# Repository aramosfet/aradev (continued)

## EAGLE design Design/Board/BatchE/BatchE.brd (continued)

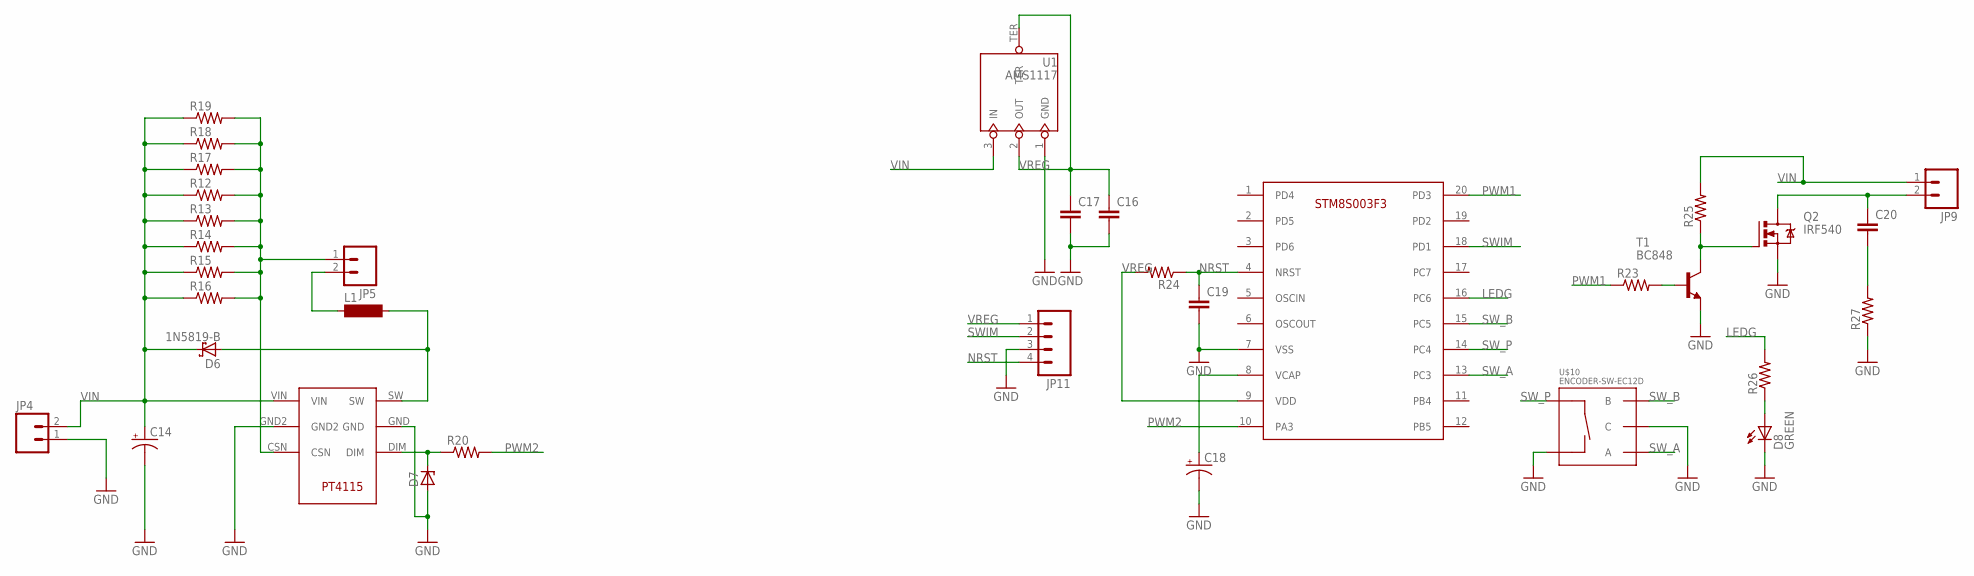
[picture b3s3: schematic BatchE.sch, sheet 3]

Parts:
C14: CAP_POLPTH4; CPOL-RADIAL-1000UF-25V
C16, C17, C19, C20: CAP1206; 1206
C18: CAP_POLPTH2; CPOL-RADIAL-10UF-25V
D6: 1N5819-B; DO41-7.6
D7: ZENER-DIODEZD-7.5; ZDIO-7.5
D8: GREEN; LED-1206
JP4, JP5, JP9: M02LOCK_LONGPADS; 1X02_LOCK_LONGPADS
JP11: M04PTH; 1X04
L1: BS11
Q2: IRF540; TO220BV
R12, R13, R14, R15, R16, R17, R18, R19, R20: RESISTOR1206; 1206
R23, R24, R25, R26, R27: RESISTOR0805-RES; 0805
T1: BC848; SOT23
U1: AMS1117; SOT-223
U$6: PT4115
U$9: STM8S003F3; SSOP20
U$10: ENCODER-SW-EC12D

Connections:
GND: C14.2 (-), C16.2, C17.2, C18.2 (-), C19.2, D7.A, D8.C, JP4.1, JP11.3, Q2.S, R27.1, T1.2 (E), U1.1 (GND), U$6.GND, U$6.GND2, U$9.7 (VSS), U$10.4 (C), U$10.5 (SW-); also elsewhere on the board
LEDG: R26.2, U$9.16 (PC6)
unnamed: JP5.1, R12.2, R13.2, R14.2, R15.2, R16.2, R17.2, R18.2, R19.2, U$6.CSN
unnamed: D8.A, R26.1
unnamed: Q2.G, R25.1, T1.3 (C)
unnamed: D7.C, R20.1, U$6.DIM
unnamed: C20.2, R27.2
unnamed: D6.A, L1.2, U$6.SW
unnamed: JP5.2, L1.1
unnamed: C20.1, JP9.2, Q2.D
unnamed: C18.1 (+), U$9.8 (VCAP)
unnamed: R23.2, T1.1 (B)
NRST: C19.1, JP11.4, R24.1, U$9.4 (NRST)
PWM1: R23.1, U$9.20 (PD3)
PWM2: R20.2, U$9.10 (PA3)
SWIM: JP11.2, U$9.18 (PD1)
SW_A: U$9.13 (PC3), U$10.1 (A)
SW_B: U$9.15 (PC5), U$10.3 (B)
SW_P: U$9.14 (PC4), U$10.2 (SW+)
VIN: C14.1 (+), D6.C, JP4.2, JP9.1, R12.1, R13.1, R14.1, R15.1, R16.1, R17.1, R18.1, R19.1, R25.2, U1.3 (IN), U$6.VIN
VREG: C16.1, C17.1, JP11.1, R24.2, U1.2 (OUT), U1.TER, U$9.9 (VDD)

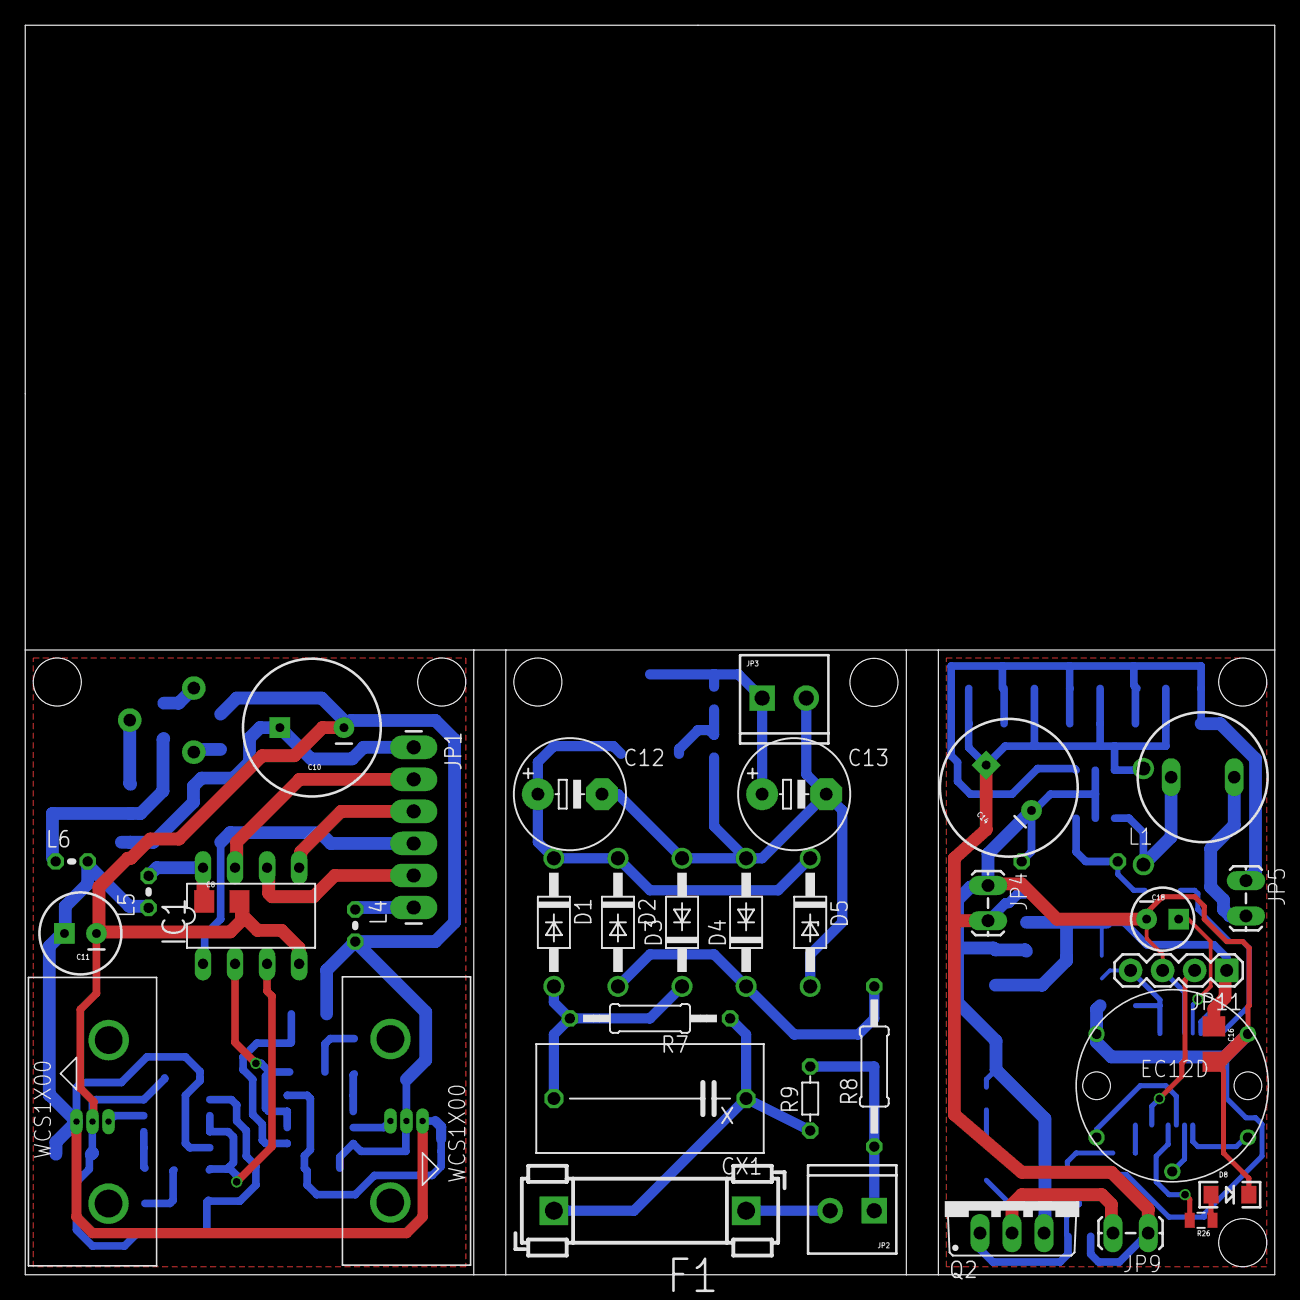
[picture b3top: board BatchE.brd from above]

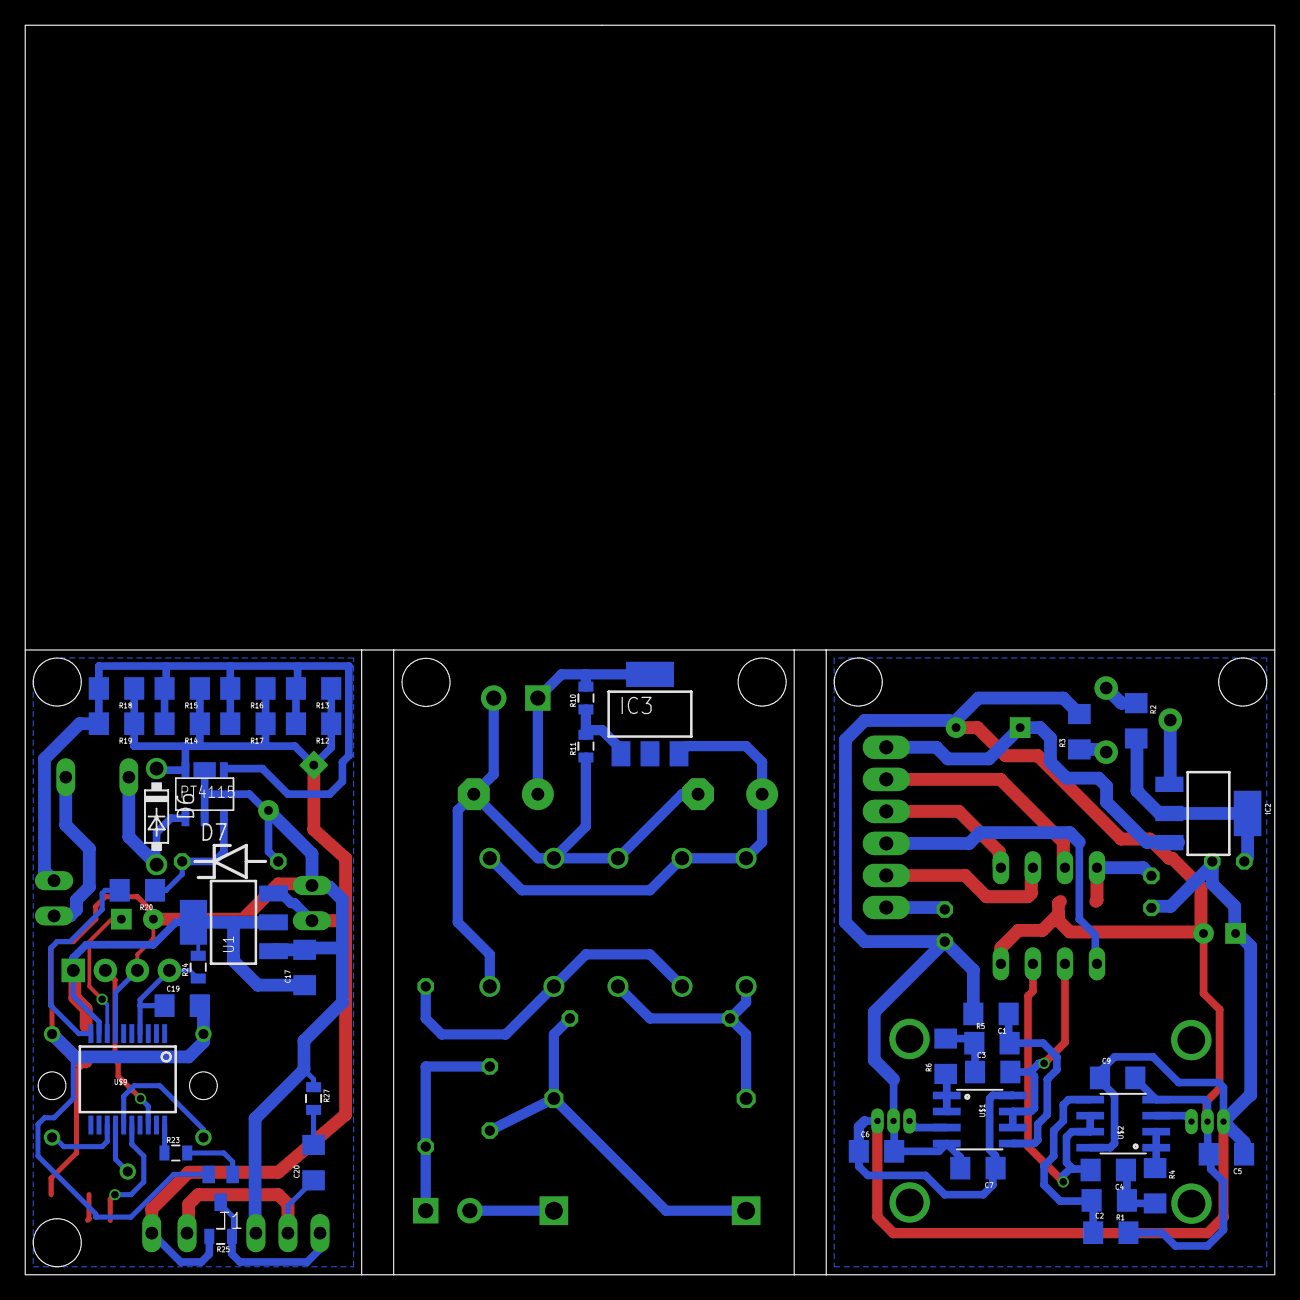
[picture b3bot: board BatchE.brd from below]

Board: 2 copper layers, 99.1 x 99.1 mm, 79 parts (42 on the bottom side), 52 nets.

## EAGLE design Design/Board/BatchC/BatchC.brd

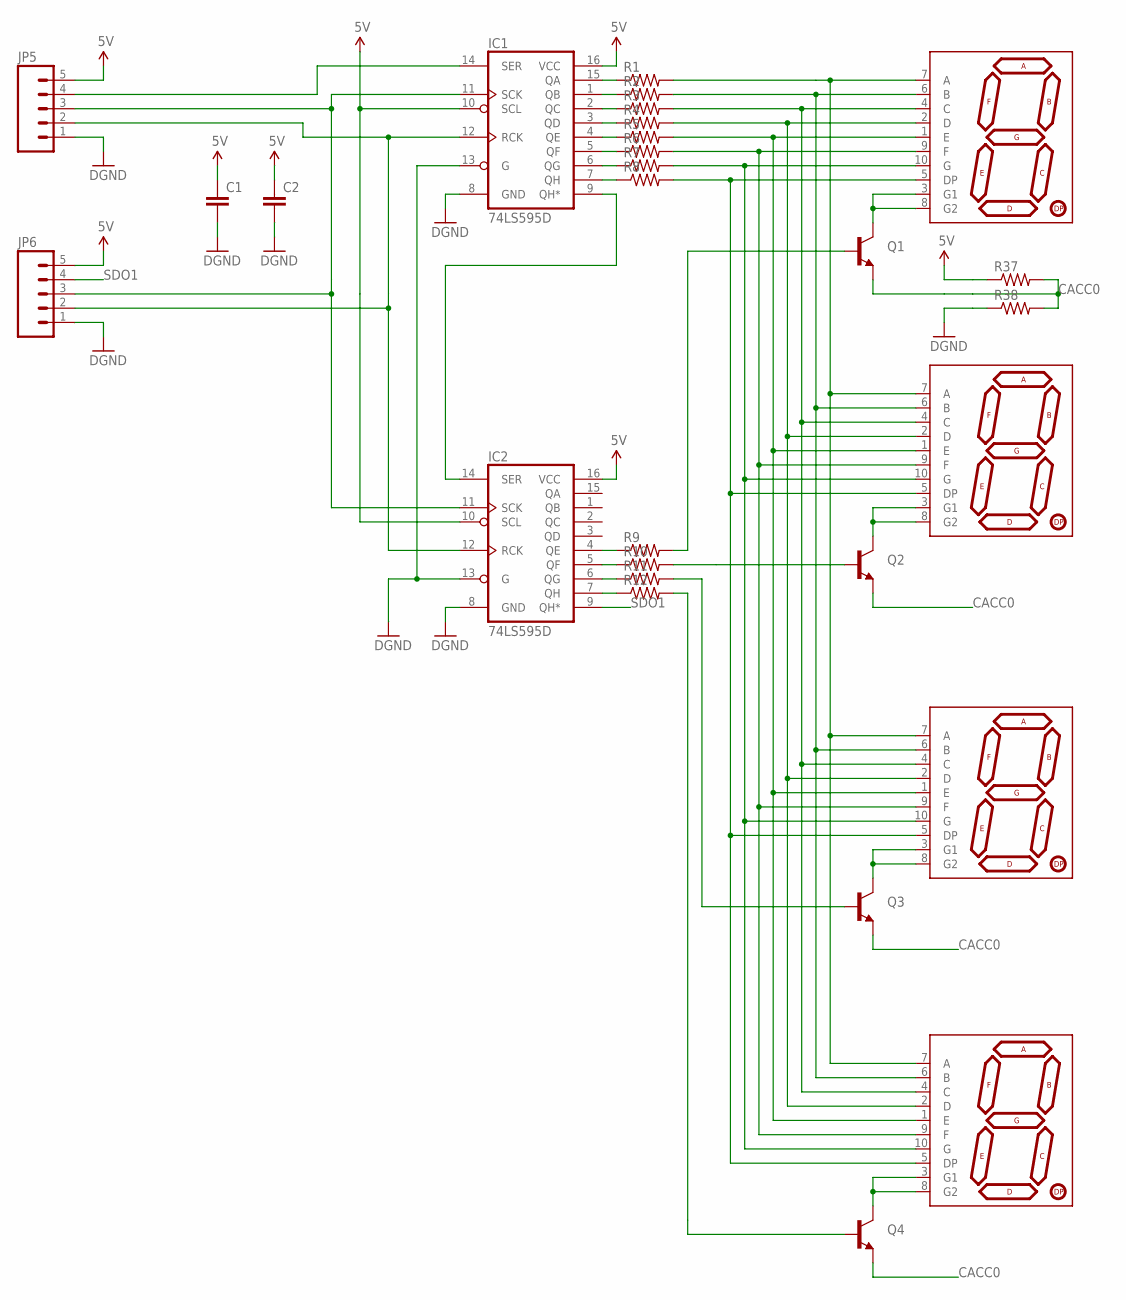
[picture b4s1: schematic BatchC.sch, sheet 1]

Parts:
C1, C2: CAP1206; 1206
IC1, IC2: 74LS595D; SO16
JP5, JP6: M05PTH; 1X05
Q1, Q2, Q3, Q4: TRANSISTOR_NPNSOT23; SOT23
R1, R2, R3, R4, R5, R6, R7, R8, R9, R10, R11, R12, R37, R38: RESISTOR0805-RES; 0805
U$1, U$2, U$3, U$4: 7-SEGMENT-DISPLAYPTH; 7-SEGMENT-DISPLAY

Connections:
5V: C1.1, C2.1, IC1.10 (SCL), IC1.16 (VCC), IC2.10 (SCL), IC2.16 (VCC), JP5.5, JP6.5, R37.1; also elsewhere on the board
CACC0: Q1.2 (E), Q2.2 (E), Q3.2 (E), Q4.2 (E), R37.2, R38.2
GND: C1.2, C2.2, IC1.8 (GND), IC1.13 (G), IC2.8 (GND), IC2.13 (G), JP5.1, JP6.1, R38.1; also elsewhere on the board
unnamed: Q2.3 (C), U$1.3 (G1), U$1.8 (G2)
unnamed: Q3.3 (C), U$2.3 (G1), U$2.8 (G2)
unnamed: Q4.3 (C), U$4.3 (G1), U$4.8 (G2)
unnamed: R4.2, U$1.2 (D), U$2.2 (D), U$3.2 (D), U$4.2 (D)
unnamed: R5.2, U$1.1 (E), U$2.1 (E), U$3.1 (E), U$4.1 (E)
unnamed: R6.2, U$1.9 (F), U$2.9 (F), U$3.9 (F), U$4.9 (F)
unnamed: R7.2, U$1.10 (G), U$2.10 (G), U$3.10 (G), U$4.10 (G)
unnamed: R8.2, U$1.5 (DP), U$2.5 (DP), U$3.5 (DP), U$4.5 (DP)
unnamed: IC1.15 (QA), R1.1
unnamed: IC1.1 (QB), R2.1
unnamed: IC1.2 (QC), R3.1
unnamed: IC1.3 (QD), R4.1
unnamed: IC1.4 (QE), R5.1
unnamed: IC1.5 (QF), R6.1
unnamed: IC1.6 (QG), R7.1
unnamed: IC1.7 (QH), R8.1
unnamed: Q1.3 (C), U$3.3 (G1), U$3.8 (G2)
unnamed: R3.2, U$1.4 (C), U$2.4 (C), U$3.4 (C), U$4.4 (C)
unnamed: R2.2, U$1.6 (B), U$2.6 (B), U$3.6 (B), U$4.6 (B)
unnamed: R1.2, U$1.7 (A), U$2.7 (A), U$3.7 (A), U$4.7 (A)
unnamed: IC2.7 (QH), R12.1
unnamed: IC2.6 (QG), R11.1
unnamed: IC2.5 (QF), R10.1
unnamed: IC2.4 (QE), R9.1
unnamed: Q3.1 (B), R11.2
unnamed: Q2.1 (B), R10.2
unnamed: Q4.1 (B), R12.2
unnamed: Q1.1 (B), R9.2
unnamed: IC1.12 (RCK), IC2.12 (RCK), JP5.2, JP6.2
unnamed: IC1.14 (SER), JP5.4
unnamed: IC1.11 (SCK), IC2.11 (SCK), JP5.3, JP6.3
unnamed: IC1.9 (QH*), IC2.14 (SER)
SDO1: IC2.9 (QH*), JP6.4

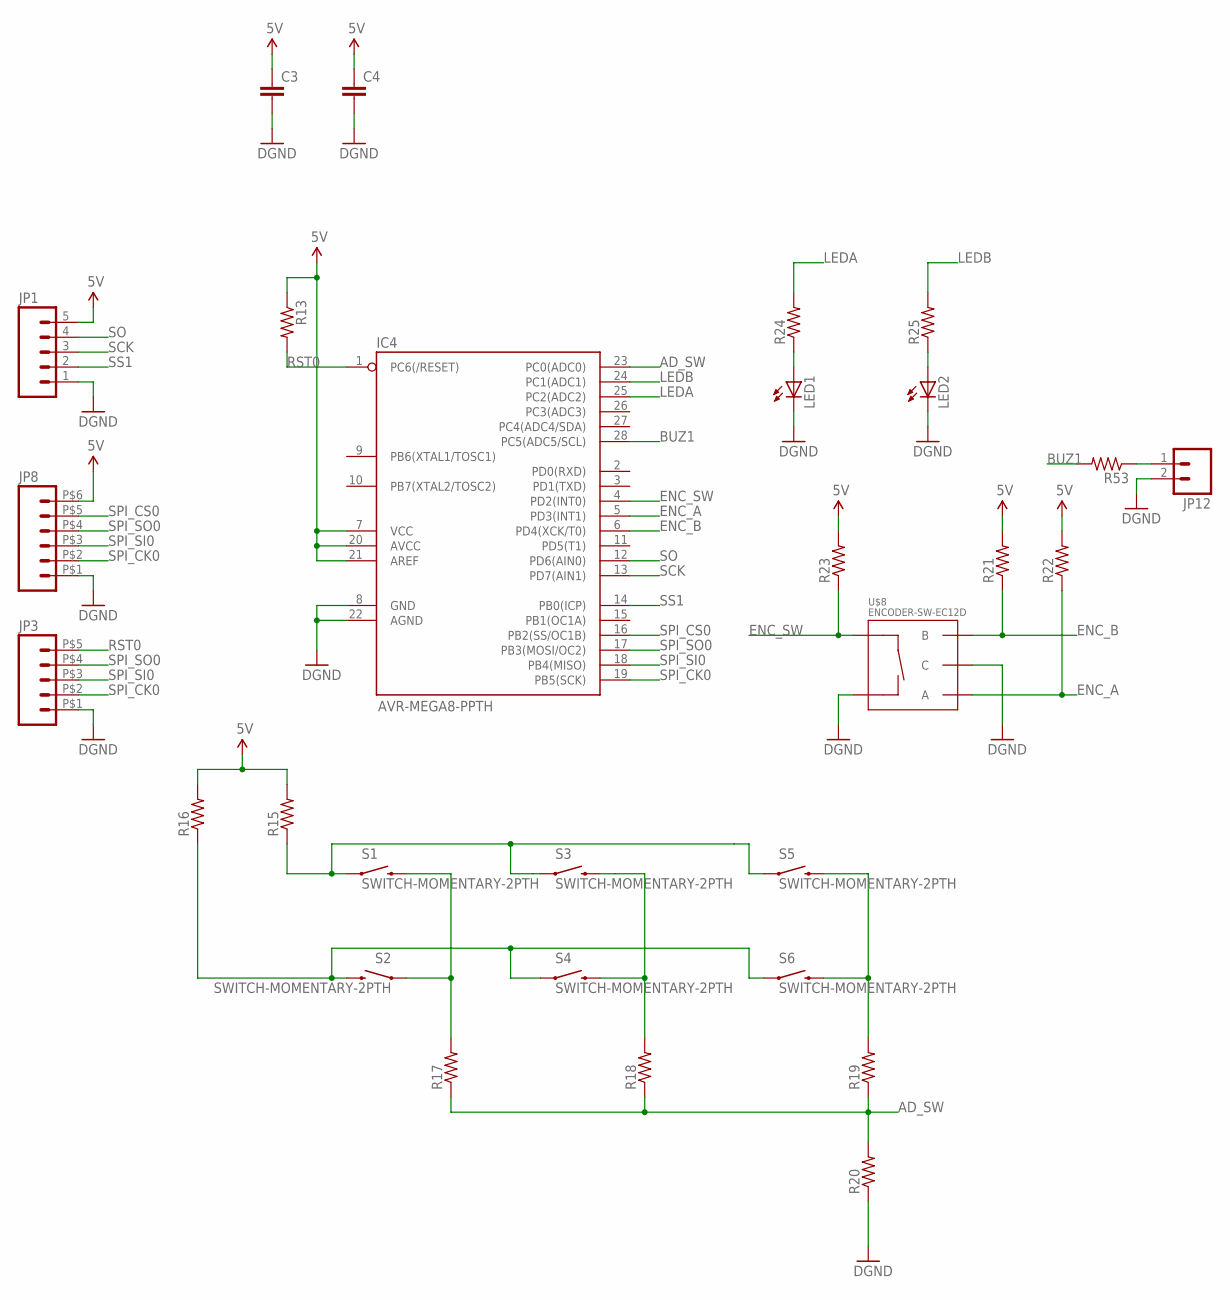
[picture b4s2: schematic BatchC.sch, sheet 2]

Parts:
C3, C4: CAP1206; 1206
IC4: AVR-MEGA8-PPTH; DIL28-3
JP1: M05PTH; 1X05
JP3: M05; 1X05_SMALLPADS
JP8: M06; 1X06_SMALLPADS
JP12: M02PTH; 1X02
LED1, LED2: LED3MM
R13, R15, R16, R17, R18, R19, R20, R21, R22, R23, R24, R25, R53: RESISTOR0805-RES; 0805
S1, S2, S3, S4, S5, S6: SWITCH-MOMENTARY-2PTH; TACTILE-PTH
U$8: ENCODER-SW-EC12D

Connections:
5V: C3.1, C4.1, IC4.7 (VCC), IC4.20 (AVCC), IC4.21 (AREF), JP1.5, JP8.P$6 (6), R13.1, R15.2, R16.2, R21.2, R22.2, R23.2; also elsewhere on the board
AD_SW: IC4.23 (PC0(ADC0)), R17.1, R18.1, R19.1, R20.2
BUZ1: IC4.28 (PC5(ADC5/SCL)), R53.2
ENC_A: IC4.5 (PD3(INT1)), R22.1, U$8.1 (A)
ENC_B: IC4.6 (PD4(XCK/T0)), R21.1, U$8.3 (B)
ENC_SW: IC4.4 (PD2(INT0)), R23.1, U$8.2 (SW+)
GND: C3.2, C4.2, IC4.8 (GND), IC4.22 (AGND), JP1.1, JP3.P$1 (1), JP8.P$1 (1), JP12.2, LED1.K (C), LED2.K (C), R20.1, U$8.4 (C), U$8.5 (SW-); also elsewhere on the board
LEDA: IC4.25 (PC2(ADC2)), R24.2
LEDB: IC4.24 (PC1(ADC1)), R25.2
unnamed: R17.2, S1.3 (2), S2.1
unnamed: R16.1, S2.3 (2), S4.1, S6.1
unnamed: R15.1, S1.1, S3.1, S5.1
unnamed: R18.2, S3.3 (2), S4.3 (2)
unnamed: R19.2, S5.3 (2), S6.3 (2)
unnamed: LED1.A, R24.1
unnamed: LED2.A, R25.1
unnamed: JP12.1, R53.1
RST0: IC4.1 (PC6(/RESET)), JP3.P$5 (5), R13.2
SCK: IC4.13 (PD7(AIN1)), JP1.3
SO: IC4.12 (PD6(AIN0)), JP1.4
SPI_CK0: IC4.19 (PB5(SCK)), JP3.P$2 (2), JP8.P$2 (2)
SPI_CS0: IC4.16 (PB2(SS/OC1B)), JP8.P$5 (5)
SPI_SI0: IC4.18 (PB4(MISO)), JP3.P$3 (3), JP8.P$3 (3)
SPI_SO0: IC4.17 (PB3(MOSI/OC2)), JP3.P$4 (4), JP8.P$4 (4)
SS1: IC4.14 (PB0(ICP)), JP1.2

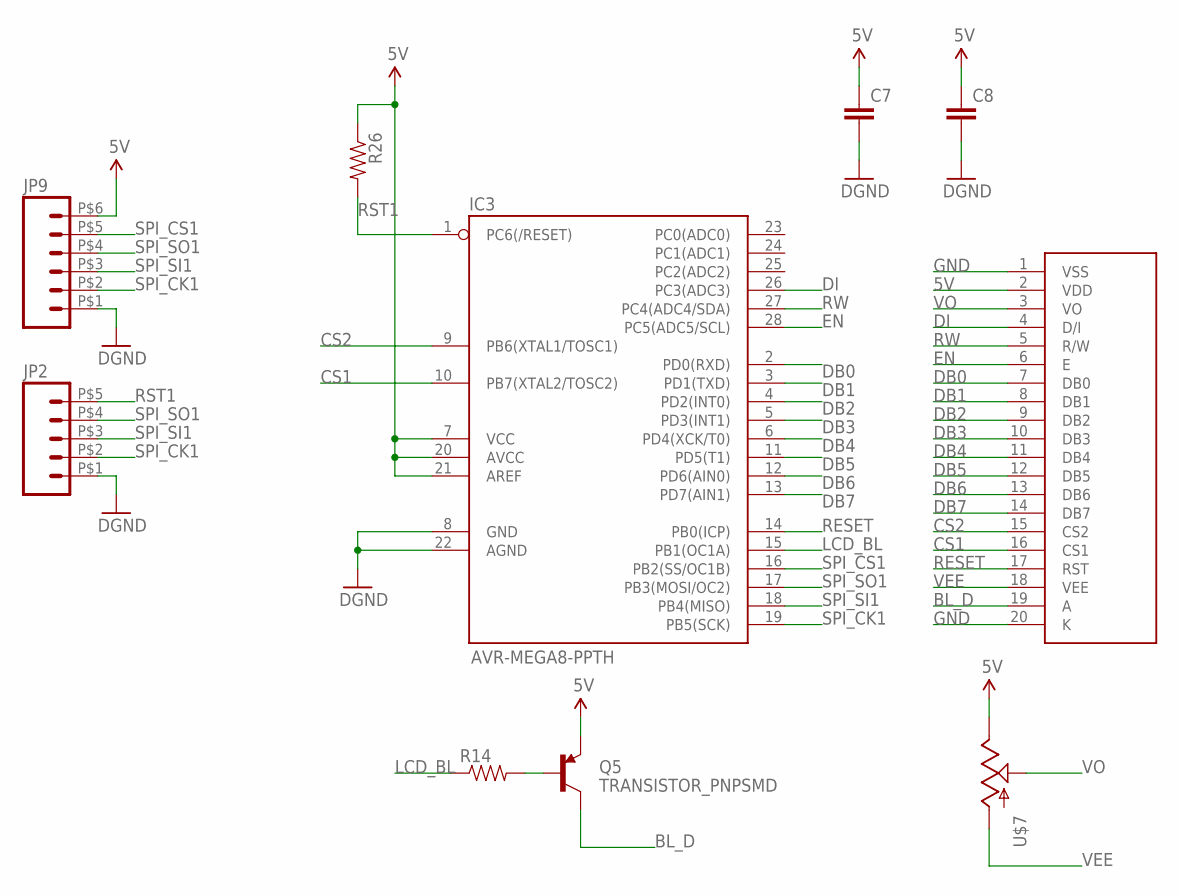
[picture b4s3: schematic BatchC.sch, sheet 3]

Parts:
C7, C8: CAP1206; 1206
IC3: AVR-MEGA8-PPTH; DIL28-3
JP2: M05; 1X05_SMALLPADS
JP9: M06; 1X06_SMALLPADS
Q5: TRANSISTOR_PNPSMD; SOT23-3
R14, R26: RESISTOR0805-RES; 0805
U$7: POTTRIM; TRIM_POT
U$9: LCD-G12864BARE; 1X20

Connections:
5V: C7.1, C8.1, IC3.7 (VCC), IC3.20 (AVCC), IC3.21 (AREF), JP9.P$6 (6), Q5.2 (E), R26.1, U$7.2 (E), U$9.2 (VDD); also elsewhere on the board
BL_D: Q5.3 (C), U$9.19 (A)
CS1: IC3.10 (PB7(XTAL2/TOSC2)), U$9.16 (CS1)
CS2: IC3.9 (PB6(XTAL1/TOSC1)), U$9.15 (CS2)
DB0: IC3.2 (PD0(RXD)), U$9.7 (DB0)
DB1: IC3.3 (PD1(TXD)), U$9.8 (DB1)
DB2: IC3.4 (PD2(INT0)), U$9.9 (DB2)
DB3: IC3.5 (PD3(INT1)), U$9.10 (DB3)
DB4: IC3.6 (PD4(XCK/T0)), U$9.11 (DB4)
DB5: IC3.11 (PD5(T1)), U$9.12 (DB5)
DB6: IC3.12 (PD6(AIN0)), U$9.13 (DB6)
DB7: IC3.13 (PD7(AIN1)), U$9.14 (DB7)
DI: IC3.26 (PC3(ADC3)), U$9.4 (D/I)
EN: IC3.28 (PC5(ADC5/SCL)), U$9.6 (E)
GND: C7.2, C8.2, IC3.8 (GND), IC3.22 (AGND), JP2.P$1 (1), JP9.P$1 (1), U$9.1 (VSS), U$9.20 (K); also elsewhere on the board
LCD_BL: IC3.15 (PB1(OC1A)), R14.1
unnamed: Q5.1 (B), R14.2
RESET: IC3.14 (PB0(ICP)), U$9.17 (RST)
RST1: IC3.1 (PC6(/RESET)), JP2.P$5 (5), R26.2
RW: IC3.27 (PC4(ADC4/SDA)), U$9.5 (R/W)
SPI_CK1: IC3.19 (PB5(SCK)), JP2.P$2 (2), JP9.P$2 (2)
SPI_CS1: IC3.16 (PB2(SS/OC1B)), JP9.P$5 (5)
SPI_SI1: IC3.18 (PB4(MISO)), JP2.P$3 (3), JP9.P$3 (3)
SPI_SO1: IC3.17 (PB3(MOSI/OC2)), JP2.P$4 (4), JP9.P$4 (4)
VEE: U$7.3 (A), U$9.18 (VEE)
VO: U$7.1 (S), U$9.3 (VO)

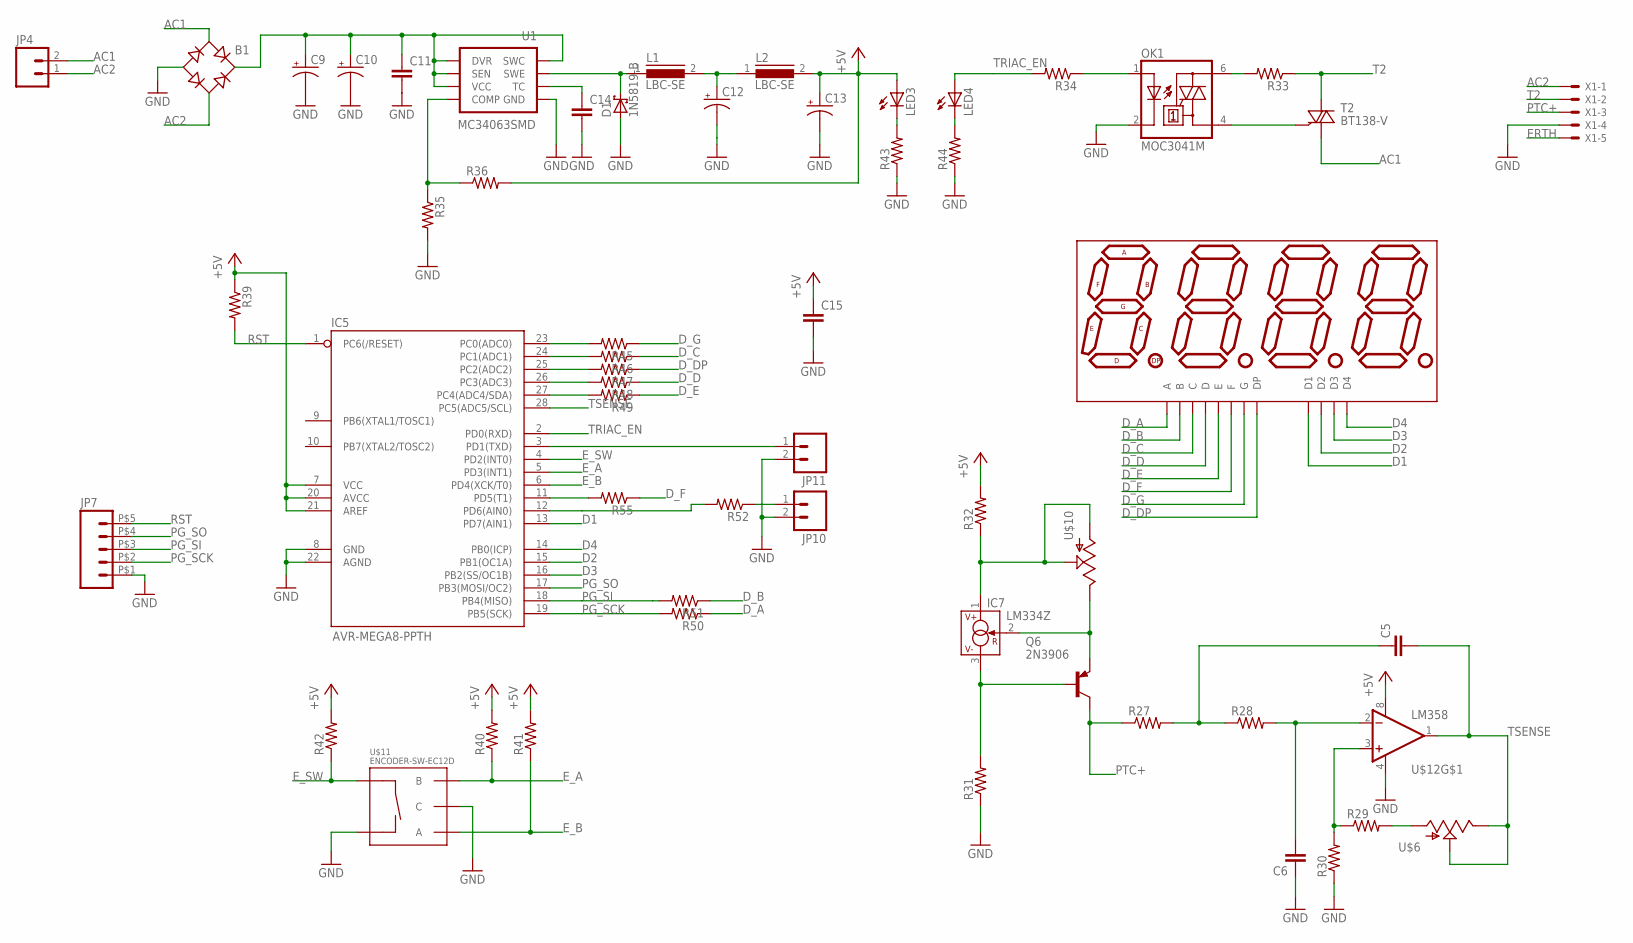
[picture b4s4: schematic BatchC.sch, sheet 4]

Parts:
B1: RB1A
C5, C6: CAPPTH; CAP-PTH-SMALL
C9, C10, C12, C13: CAP_POLPTH1; CPOL-RADIAL-100UF-25V
C11, C14, C15: CAP1206; 1206
D1: 1N5819-B; DO41-7.6
IC5: AVR-MEGA8-PPTH; DIL28-3
IC7: LM334Z; TO92
JP4: M023.5MM; SCREWTERMINAL-3.5MM-2
JP7: M05; 1X05_SMALLPADS
JP10, JP11: M02PTH; 1X02
L1, L2: LBC-SE
LED3, LED4: LED3MM
OK1: MOC3041M; DIL06
Q6: 2N3906; TO92
R27, R28, R29, R30, R31, R32, R33, R34, R35, R36, R39, R40, R41, R42, R43, R44, R45, R46, R47, R48, R49, R50, R51, R52, R55: RESISTOR0603-RES; 0603-RES
T2: BT138-V; TO220BV
U1: MC34063SMD; SO08
U$5: 7-SEGMENT-4DIGIT-COUNTER; 7-SEGMENT-4DIGIT-TPS
U$6, U$10: POTTRIM; TRIM_POT
U$11: ENCODER-SW-EC12D
U$12: LM358; DIP08
X1: KK-156-5

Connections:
+5V: C13.1 (+), C15.1, IC5.7 (VCC), IC5.20 (AVCC), IC5.21 (AREF), L2.2, LED3.A, R32.2, R36.2, R39.1, R40.2, R41.2, R42.2, U$12.8 (V+)
AC1: B1.AC1, JP4.2, T2.T1 (A1)
AC2: B1.AC2, JP4.1, X1.1
D1: IC5.13 (PD7(AIN1)), U$5.P$12 (D1)
D2: IC5.15 (PB1(OC1A)), U$5.P$9 (D2)
D3: IC5.16 (PB2(SS/OC1B)), U$5.P$8 (D3)
D4: IC5.14 (PB0(ICP)), U$5.P$6 (D4)
D_A: R50.1, U$5.P$11 (A)
D_B: R51.1, U$5.P$7 (B)
D_C: R46.1, U$5.P$4 (C)
D_D: R48.1, U$5.P$2 (D)
D_DP: R47.1, U$5.P$3 (DP)
D_E: R49.1, U$5.P$1 (E)
D_F: R55.1, U$5.P$10 (F)
D_G: R45.1, U$5.P$5 (G)
ERTH: X1.5
E_A: IC5.5 (PD3(INT1)), R40.1, U$11.3 (B)
E_B: IC5.6 (PD4(XCK/T0)), R41.1, U$11.1 (A)
E_SW: IC5.4 (PD2(INT0)), R42.1, U$11.2 (SW+)
GND: B1.-, C6.1, C9.2 (-), C10.2 (-), C11.2, C12.2 (-), C13.2 (-), C14.2, C15.2, D1.A, IC5.8 (GND), IC5.22 (AGND), JP7.P$1 (1), JP10.2, JP11.2, OK1.2 (C), R30.1, R31.1, R35.2, R43.1, R44.1, U1.4 (GND), U$11.4 (C), U$11.5 (SW-), U$12.4 (V-), X1.4; also elsewhere on the board
unnamed: IC7.3 (V-), Q6.2 (B), R31.2
unnamed: IC7.1 (V+), R32.1, U$10.1 (S), U$10.3 (A)
unnamed: IC5.24 (PC1(ADC1)), R46.2
unnamed: IC7.2 (R), Q6.3 (E), U$10.2 (E)
unnamed: OK1.1 (A), R34.1
unnamed: OK1.6 (A2), R33.2
unnamed: C5.1, R27.2, R28.1
unnamed: C6.2, R28.2, U$12.2 (-IN)
unnamed: IC5.25 (PC2(ADC2)), R47.2
unnamed: R29.2, U$6.3 (A)
unnamed: LED3.K (C), R43.2
unnamed: R29.1, R30.2, U$12.3 (+IN)
unnamed: OK1.4 (A1), T2.G
unnamed: LED4.K (C), R44.2
unnamed: B1.+, C9.1 (+), C10.1 (+), C11.1, U1.1 (SWC), U1.6 (VCC), U1.7 (SEN), U1.8 (DVR)
unnamed: C14.1, U1.3 (TC)
unnamed: D1.C, L1.1, U1.2 (SWE)
unnamed: C12.1 (+), L1.2, L2.1
unnamed: R35.1, R36.1, U1.5 (COMP)
unnamed: IC5.26 (PC3(ADC3)), R48.2
unnamed: IC5.27 (PC4(ADC4/SDA)), R49.2
unnamed: IC5.23 (PC0(ADC0)), R45.2
unnamed: IC5.11 (PD5(T1)), R55.2
unnamed: IC5.12 (PD6(AIN0)), R52.2
unnamed: JP10.1, R52.1
unnamed: IC5.3 (PD1(TXD)), JP11.1
PG_SCK: IC5.19 (PB5(SCK)), JP7.P$2 (2), R50.2
PG_SI: IC5.18 (PB4(MISO)), JP7.P$3 (3), R51.2
PG_SO: IC5.17 (PB3(MOSI/OC2)), JP7.P$4 (4)
PTC+: Q6.1 (C), R27.1, X1.3
RST: IC5.1 (PC6(/RESET)), JP7.P$5 (5), R39.2
T2: R33.1, T2.T2 (A2), X1.2
TRIAC_EN: IC5.2 (PD0(RXD)), LED4.A, R34.2
TSENSE: C5.2, IC5.28 (PC5(ADC5/SCL)), U$6.1 (S), U$6.2 (E), U$12.1 (OUT)

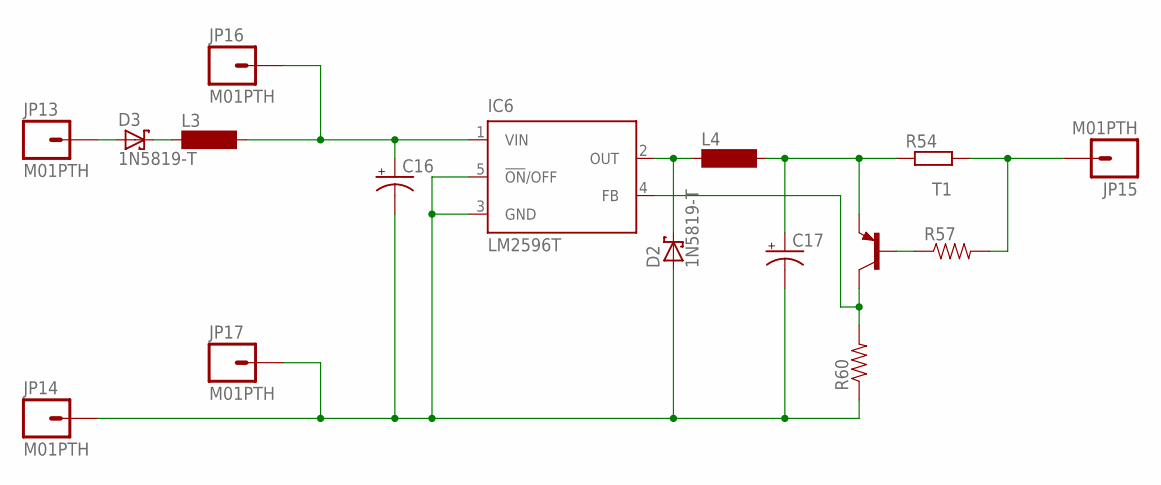
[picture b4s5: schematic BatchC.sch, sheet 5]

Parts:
C16, C17: CAP_POLPTH1; CPOL-RADIAL-100UF-25V
D2, D3: 1N5819-T; DO41-7.6
IC6: LM2596T; T05D
JP13, JP14, JP15, JP16, JP17: M01PTH; 1X01
L3, L4: BS11
R54: R-EU_0204/2V; 0204V
R57, R60: RESISTOR1206; 1206
T1: BC857C-PNP-SOT23-BEC; SOT23-BEC

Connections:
unnamed: D3.A, JP13.1
unnamed: D3.C, L3.1
unnamed: C16.1 (+), IC6.1 (VIN), JP16.1, L3.2
unnamed: C16.2 (-), C17.2 (-), D2.A, IC6.3 (GND), IC6.5 (!ON!/OFF), JP14.1, JP17.1, R60.1
unnamed: D2.C, IC6.2 (OUT), L4.1
unnamed: C17.1 (+), L4.2, R54.1, T1.E
unnamed: IC6.4 (FB), R60.2, T1.C
unnamed: R57.1, T1.B
unnamed: JP15.1, R54.2, R57.2

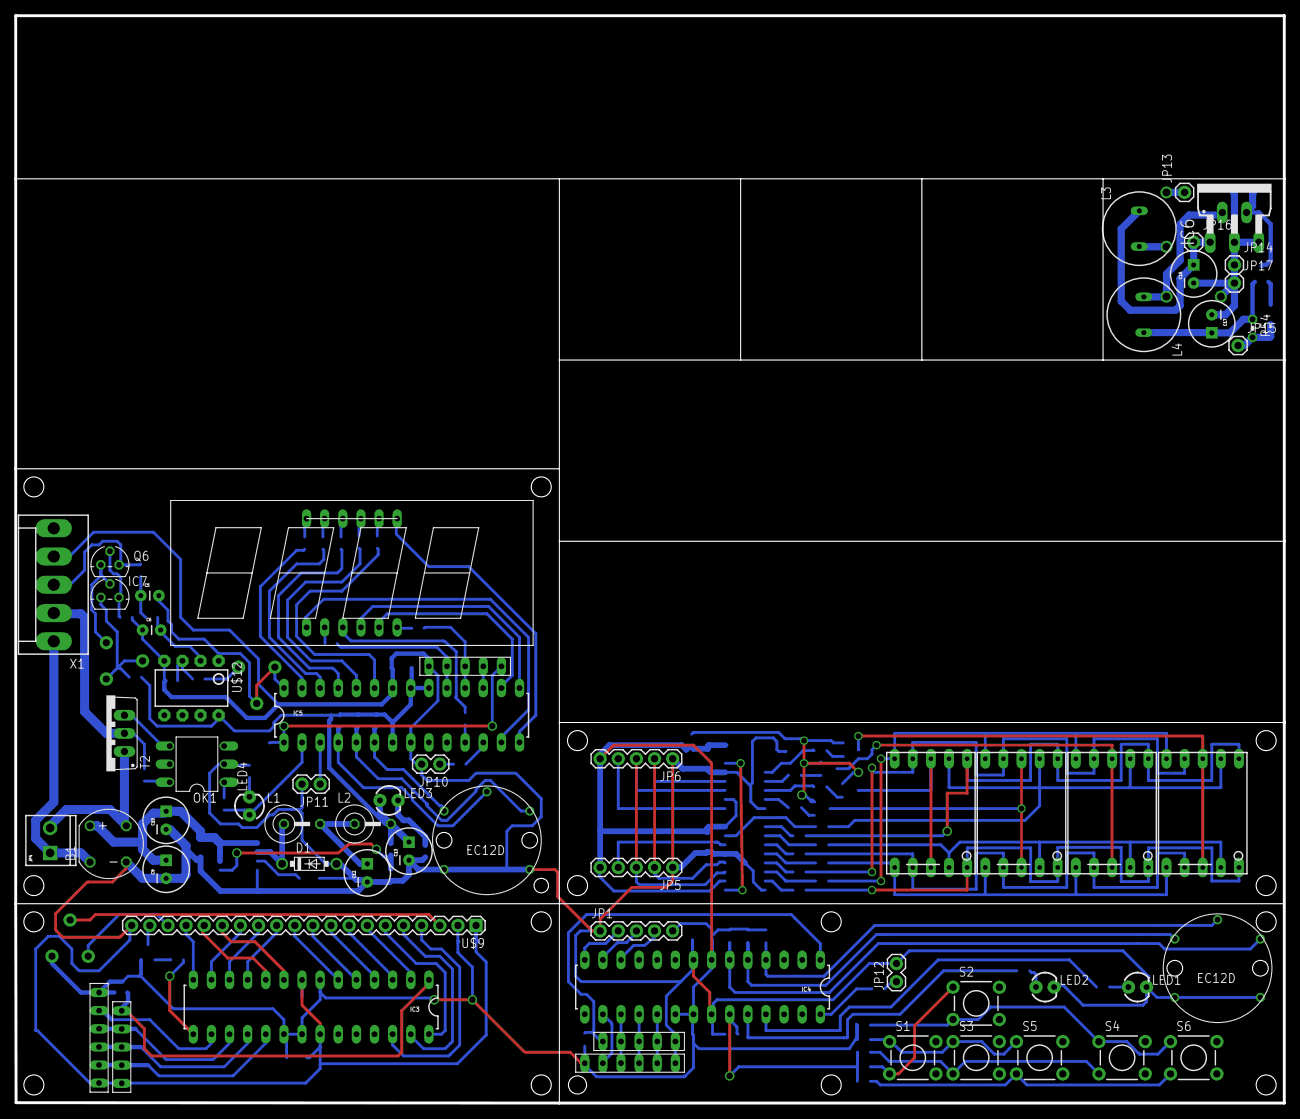
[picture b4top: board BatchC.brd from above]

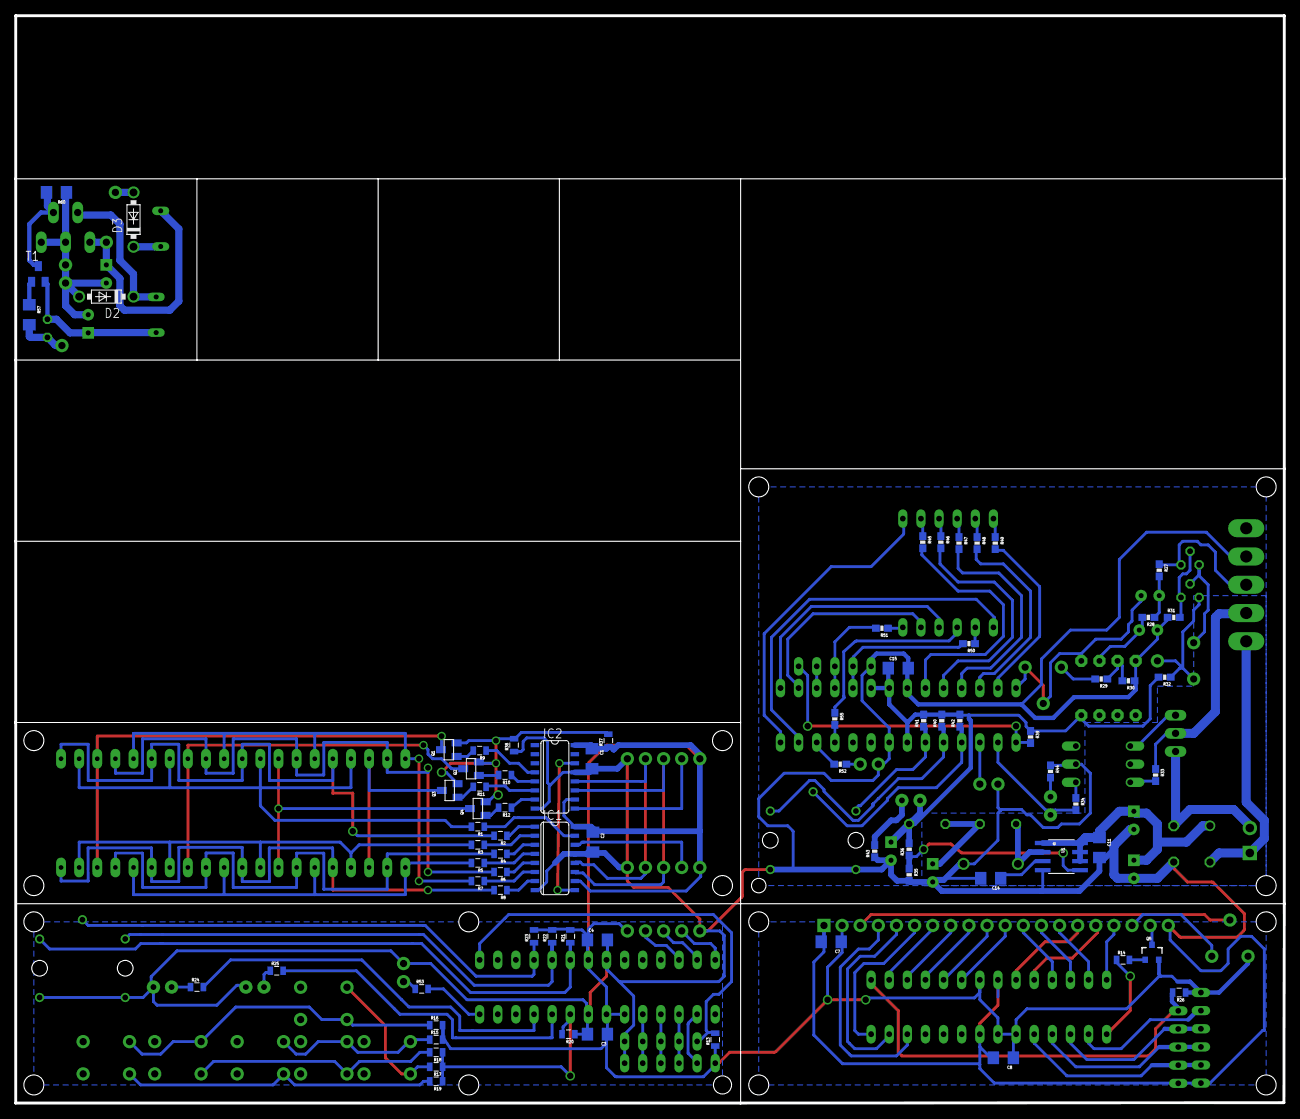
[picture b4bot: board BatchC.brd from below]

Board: 2 copper layers, 177.8 x 152.4 mm, 139 parts (76 on the bottom side), 144 nets.

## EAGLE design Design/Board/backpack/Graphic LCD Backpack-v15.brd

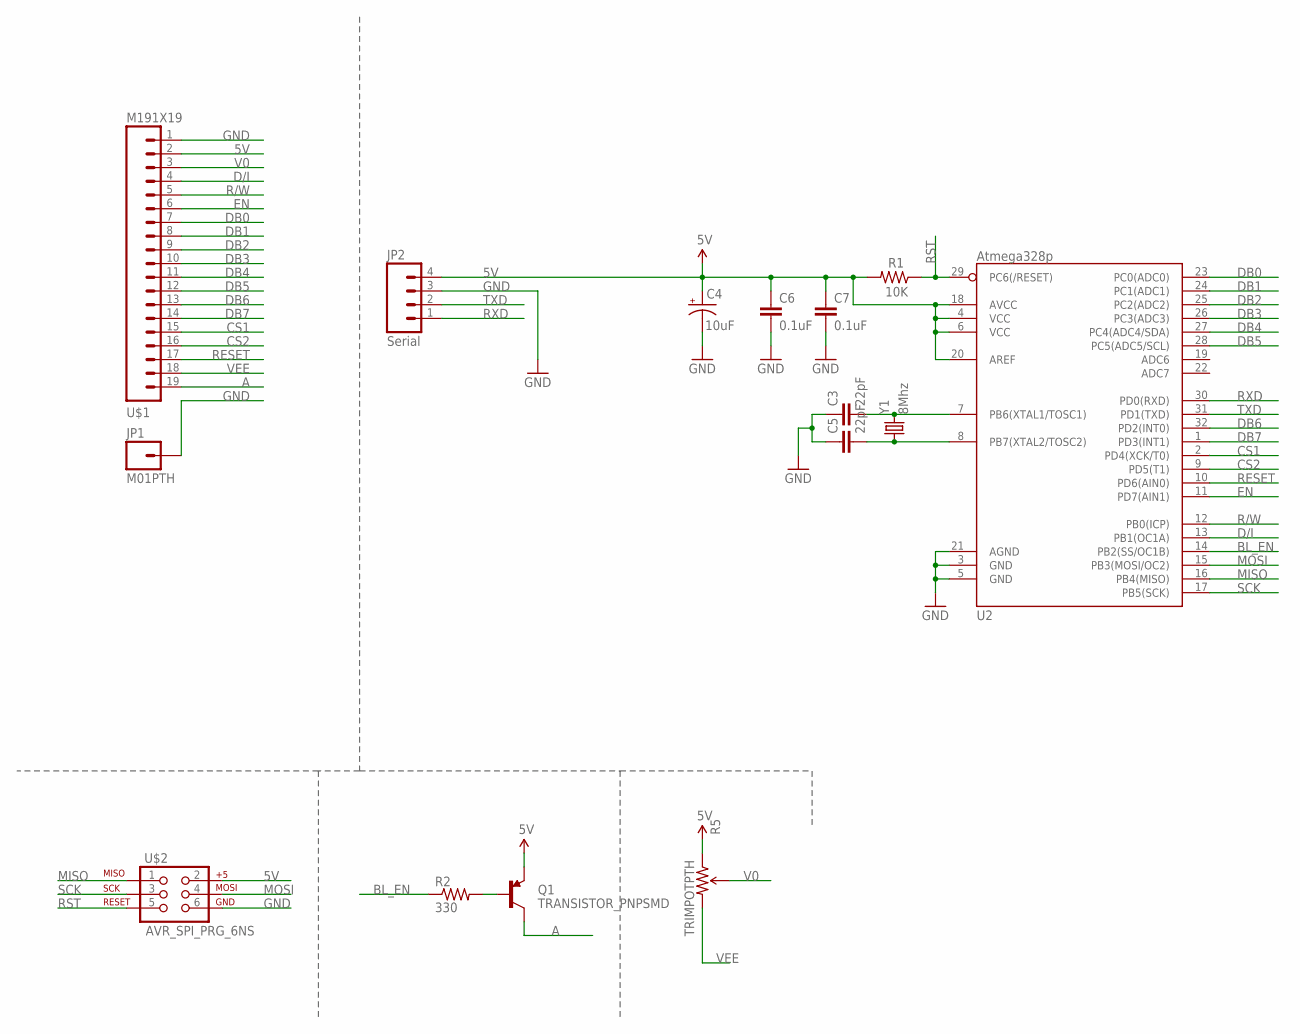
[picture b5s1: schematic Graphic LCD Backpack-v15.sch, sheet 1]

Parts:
C3, C5: 22pF; 1206
C4: 10uF; EIA3216
C6, C7: 0.1uF; 1206
JP1: M01PTH; 1X01
JP2: Serial; 1X04
Q1: TRANSISTOR_PNPSMD; SOT23-3
R1: 10K; 0805
R2: 330; 0805
R5: TRIMPOTPTH; TRIM_POT_PTH
U2: Atmega328p; TQFP32-08
U$1: M191X19; 1X19
U$2: AVR_SPI_PRG_6NS; 2X3-NS
Y1: 8Mhz; HC49US

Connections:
5V: C4.A (+), C6.1, C7.1, JP2.4, Q1.2 (E), R1.2, R5.1 (CCW), U2.4 (VCC), U2.6 (VCC), U2.18 (AVCC), U2.20 (AREF), U$1.2, U$2.2
A: Q1.3 (C), U$1.19
BL_EN: R2.1, U2.14 (PB2(SS/OC1B))
CS1: U2.2 (PD4(XCK/T0)), U$1.15
CS2: U2.9 (PD5(T1)), U$1.16
D/I: U2.13 (PB1(OC1A)), U$1.4
DB0: U2.23 (PC0(ADC0)), U$1.7
DB1: U2.24 (PC1(ADC1)), U$1.8
DB2: U2.25 (PC2(ADC2)), U$1.9
DB3: U2.26 (PC3(ADC3)), U$1.10
DB4: U2.27 (PC4(ADC4/SDA)), U$1.11
DB5: U2.28 (PC5(ADC5/SCL)), U$1.12
DB6: U2.32 (PD2(INT0)), U$1.13
DB7: U2.1 (PD3(INT1)), U$1.14
EN: U2.11 (PD7(AIN1)), U$1.6
GND: C3.1, C4.C (-), C5.1, C6.2, C7.2, JP1.1, JP2.3, U2.3 (GND), U2.5 (GND), U2.21 (AGND), U$1.1, U$2.6; also elsewhere on the board
MISO: U2.16 (PB4(MISO)), U$2.1
MOSI: U2.15 (PB3(MOSI/OC2)), U$2.4
unnamed: Q1.1 (B), R2.2
unnamed: C3.2, U2.7 (PB6(XTAL1/TOSC1)), Y1.2
unnamed: C5.2, U2.8 (PB7(XTAL2/TOSC2)), Y1.1
R/W: U2.12 (PB0(ICP)), U$1.5
RESET: U2.10 (PD6(AIN0)), U$1.17
RST: R1.1, U2.29 (PC6(/RESET)), U$2.5
RXD: JP2.1, U2.30 (PD0(RXD))
SCK: U2.17 (PB5(SCK)), U$2.3
TXD: JP2.2, U2.31 (PD1(TXD))
V0: R5.2 (WIPER), U$1.3
VEE: R5.3 (CW), U$1.18
